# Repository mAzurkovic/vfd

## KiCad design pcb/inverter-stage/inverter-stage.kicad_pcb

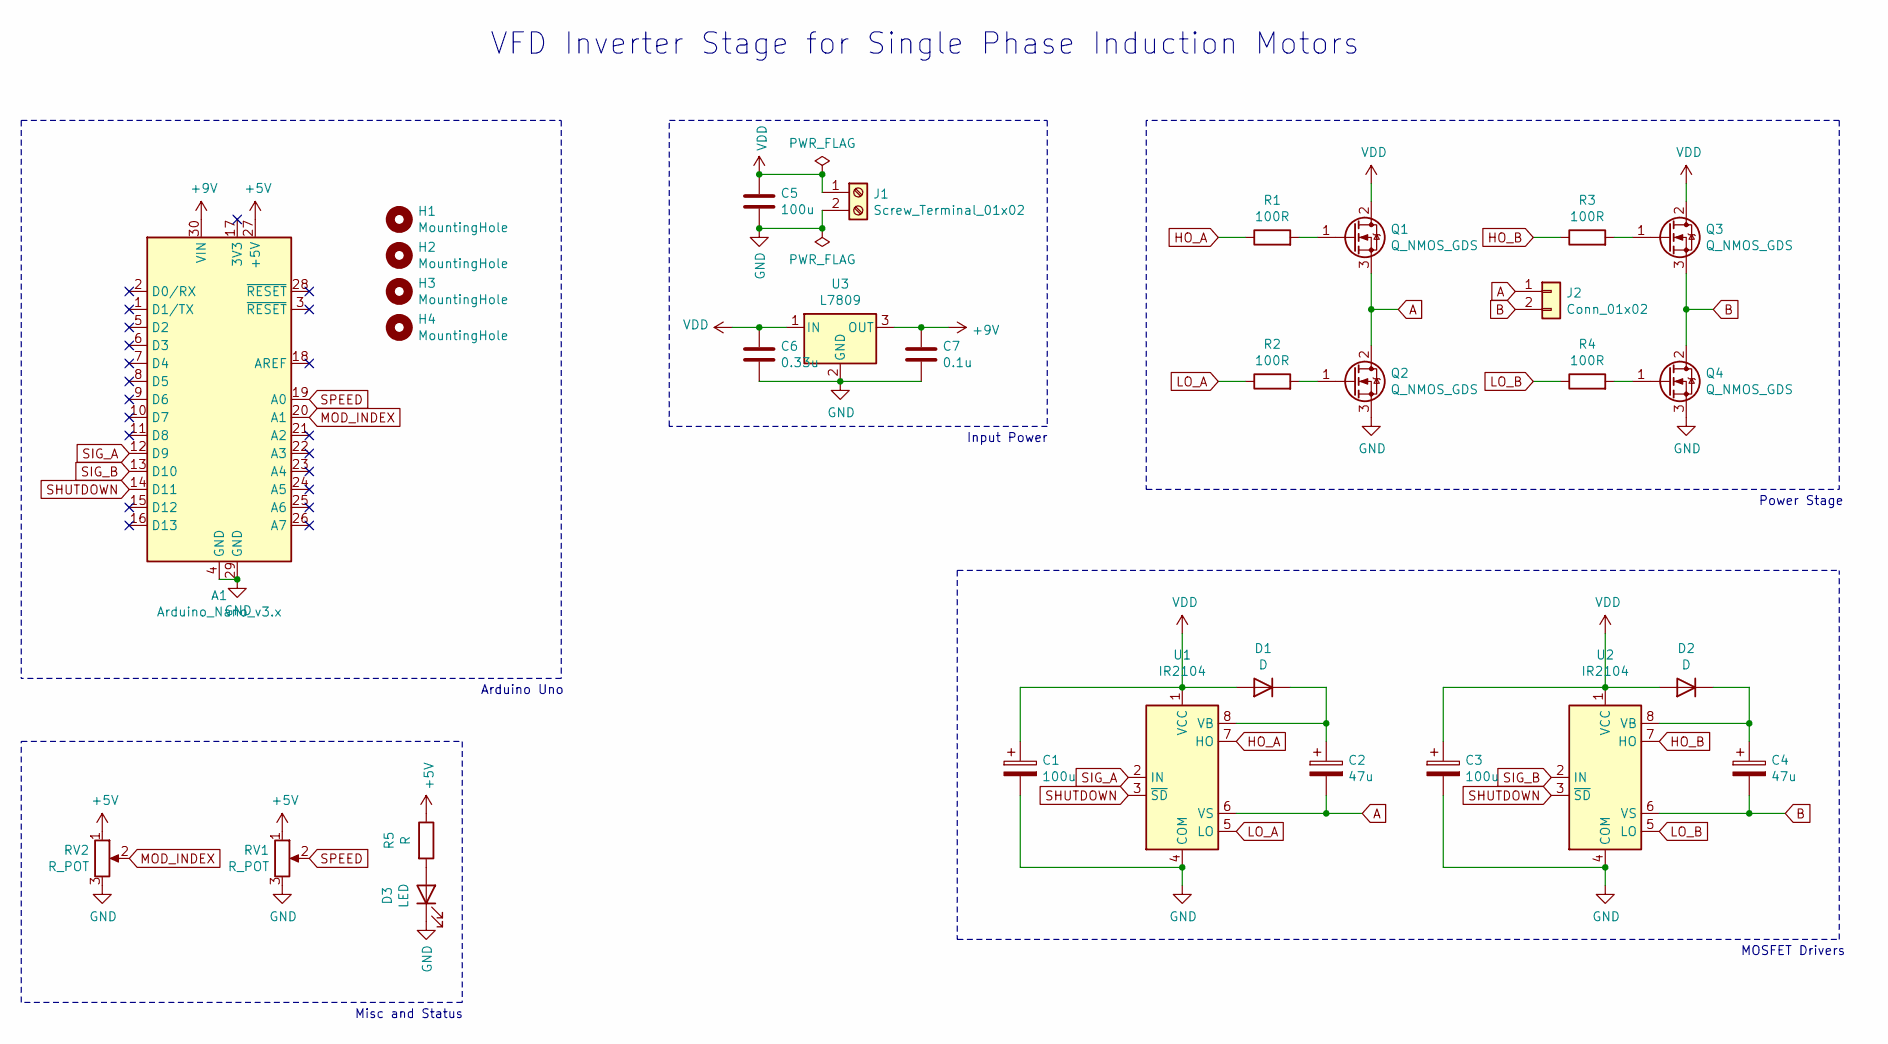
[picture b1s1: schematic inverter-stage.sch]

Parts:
A1: Arduino_Nano_v3.x; Arduino_Nano
C1, C3: 100u; CP_Radial_D6.3mm_P2.50mm
C2, C4: 47u; CP_Radial_D5.0mm_P2.50mm
C5: 100u; CP_Radial_D10.0mm_P5.00mm
C6: 0.33u; CP_Radial_D4.0mm_P2.00mm
C7: 0.1u; CP_Radial_D4.0mm_P2.00mm
D1, D2: D; D_A-405_P10.16mm_Horizontal
D3: LED; LED_D3.0mm
H1, H2, H3, H4: MountingHole; MountingHole_3.2mm_M3
J1: Screw_Terminal_01x02; TerminalBlock_Altech_AK300-2_P5.00mm
J2: Conn_01x02; TerminalBlock_Altech_AK300-2_P5.00mm
Q1, Q2, Q3, Q4: Q_NMOS_GDS; TO-220-3_Vertical
R1, R2, R3, R4: 100R; R_Axial_DIN0207_L6.3mm_D2.5mm_P7.62mm_Horizontal
R5: R; R_Axial_DIN0207_L6.3mm_D2.5mm_P7.62mm_Horizontal
RV1, RV2: R_POT; Potentiometer_Vishay_T73XW_Horizontal
U1, U2: IR2104; DIP-8_W7.62mm_Socket
U3: L7809; TO-220-3_Vertical

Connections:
+5V: A1.27 (+5V), R5.1, RV1.1, RV2.1
+9V: A1.30 (VIN), C7.1, U3.3 (OUT)
A: C2.2, J2.1, Q1.3 (S), Q2.2 (D), U1.6 (VS)
B: C4.2, J2.2, Q3.3 (S), Q4.2 (D), U2.6 (VS)
GND: A1.4 (GND), A1.29 (GND), C1.2, C3.2, C5.2, C6.2, C7.2, D3.1 (K), J1.2, Q2.3 (S), Q4.3 (S), RV1.3, RV2.3, U1.4 (COM), U2.4 (COM), U3.2 (GND)
HO_A: R1.1, U1.7 (HO)
HO_B: R3.1, U2.7 (HO)
LO_A: R2.1, U1.5 (LO)
LO_B: R4.1, U2.5 (LO)
MOD_INDEX: A1.20 (A1), RV2.2
unnamed: C2.1, D1.1 (K), U1.8 (VB)
unnamed: C4.1, D2.1 (K), U2.8 (VB)
unnamed: D3.2 (A), R5.2
unnamed: Q1.1 (G), R1.2
unnamed: Q2.1 (G), R2.2
unnamed: Q3.1 (G), R3.2
unnamed: Q4.1 (G), R4.2
SHUTDOWN: A1.14 (D11), U1.3 (~SD), U2.3 (~SD)
SIG_A: A1.12 (D9), U1.2 (IN)
SIG_B: A1.13 (D10), U2.2 (IN)
SPEED: A1.19 (A0), RV1.2
VDD: C1.1, C3.1, C5.1, C6.1, D1.2 (A), D2.2 (A), J1.1, Q1.2 (D), Q3.2 (D), U1.1 (VCC), U2.1 (VCC), U3.1 (IN)

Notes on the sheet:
Power Stage
MOSFET Drivers
Input Power
Arduino Uno
VFD Inverter Stage for Single Phase Induction Motors
Misc and Status

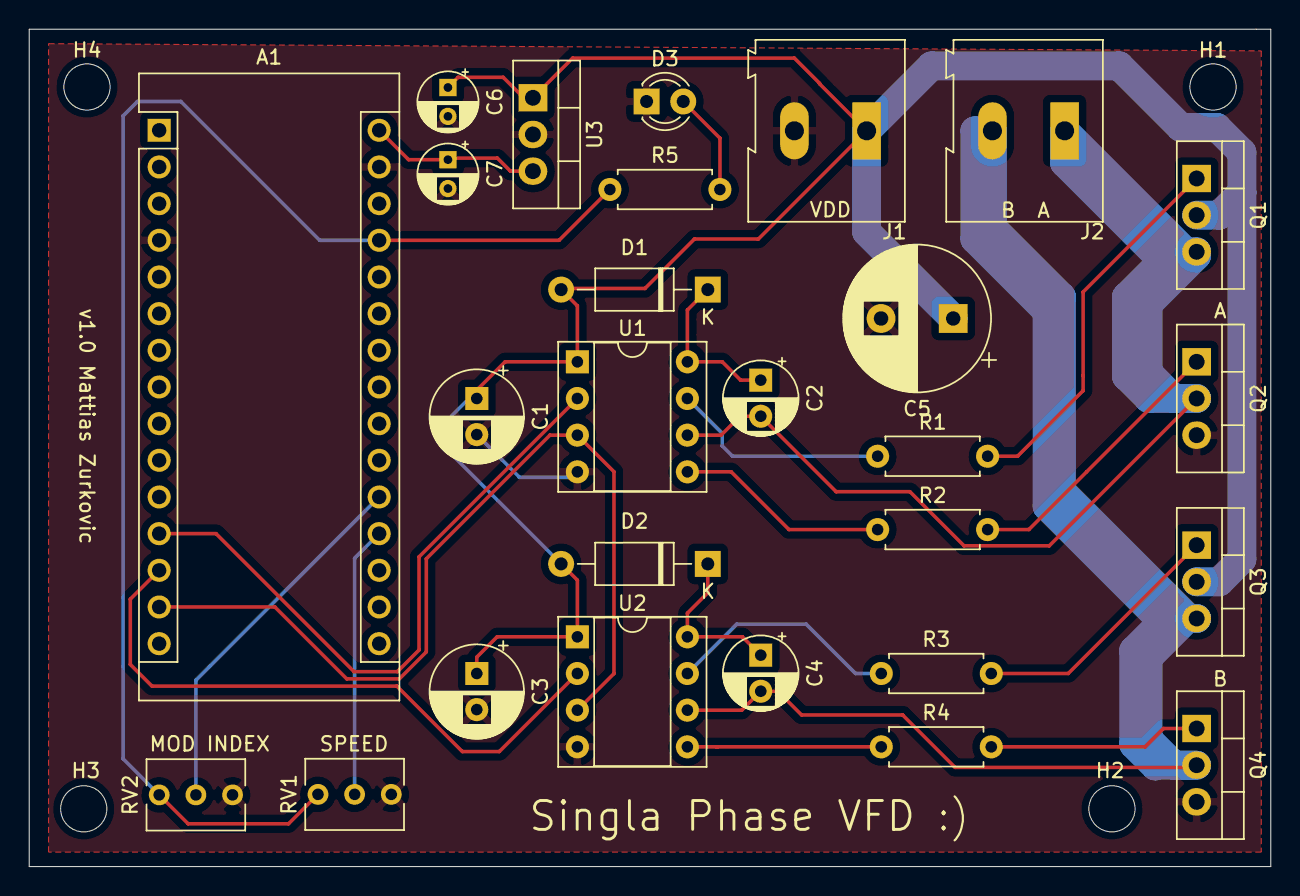
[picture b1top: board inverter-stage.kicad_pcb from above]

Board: 2 copper layers, 86.0 x 58.0 mm, 31 parts (0 on the bottom side), 22 nets.

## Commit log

2021-11-30 init
2021-11-30 create pcb files for inverter
2021-12-01 start tracing
2021-12-01 pcb ready
2021-12-01 add gerber giles
2021-12-02 first version complete - sent to fab
